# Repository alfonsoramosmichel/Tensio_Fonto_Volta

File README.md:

# Tensio_Fonto_Volta
Fuente de voltaje con salida simétrica +/-12, fija +5 y variable +1.2 - +24

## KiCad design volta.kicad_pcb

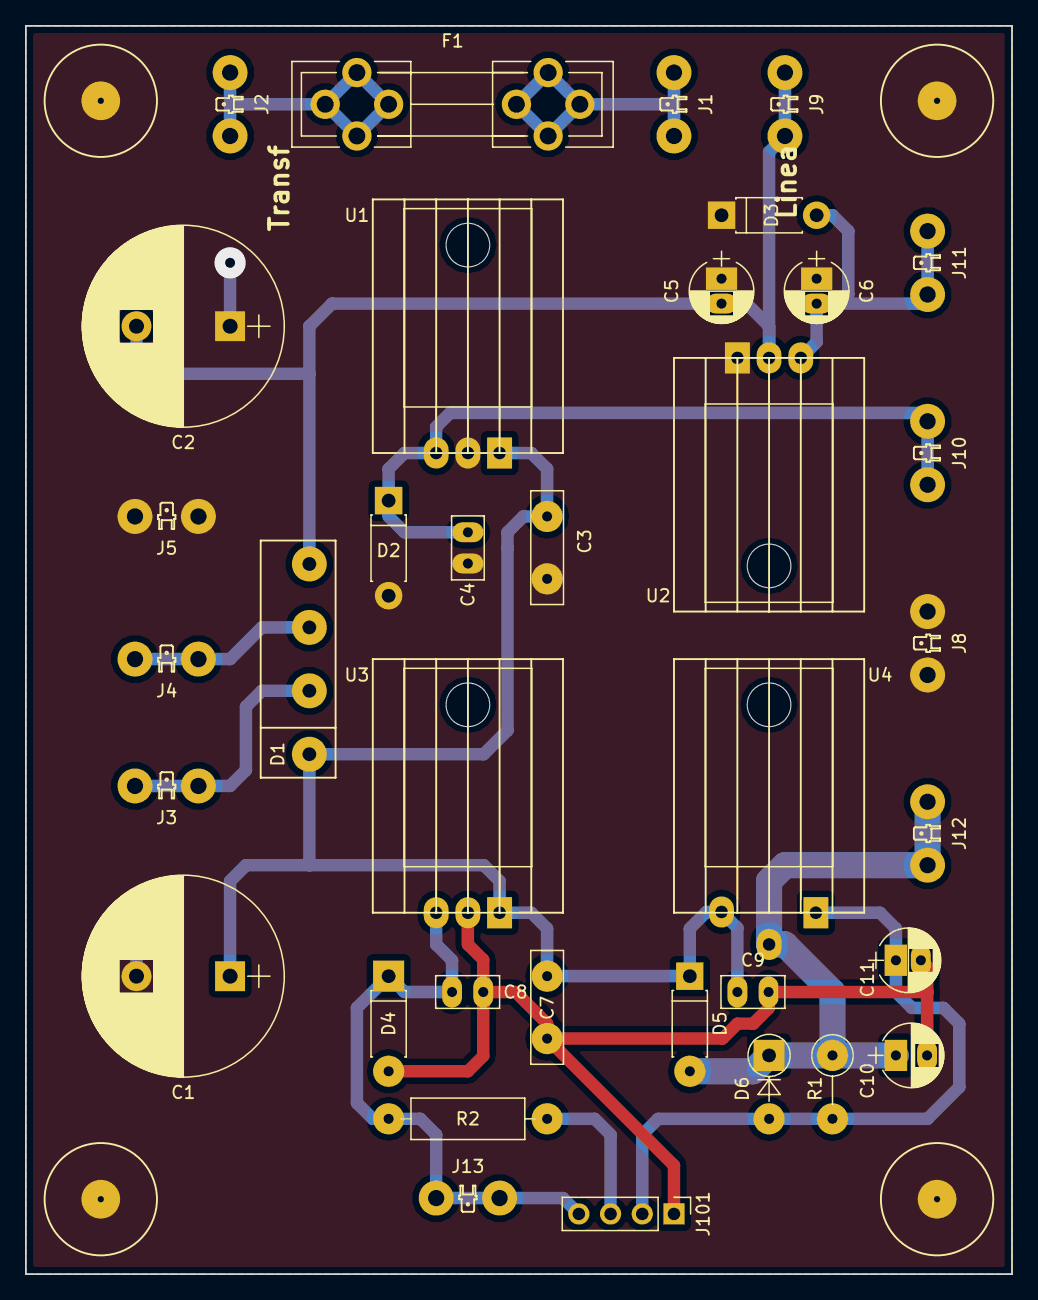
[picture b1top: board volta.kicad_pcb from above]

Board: 2 copper layers, 79.0 x 100.0 mm, 40 parts (0 on the bottom side), 14 nets.

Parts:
C1, C2: 2200uF / 50V; CP_Radial_D16.0mm_P7.50mm
C3, C7: 0.33uF; C_Disc_D9.0mm_W2.5mm_P5.00mm
C4, C8, C9: 0.1uF; C_Disc_D5.0mm_W2.5mm_P2.50mm
C5: 22uF; CP_Radial_D5.0mm_P2.00mm
C6: 1uF; CP_Radial_D5.0mm_P2.00mm
C10: 1uF; CP_Radial_D5.0mm_P2.50mm
C11: 10uF; CP_Radial_D5.0mm_P2.00mm
D1: EXI-KBL406; EXI_KBL406
D2, D3, D4, D5: 1N4007; D_DO-41_SOD81_P7.62mm_Horizontal
D6: 1N4007; D_DO-41_SOD81_P5.08mm_Vertical_AnodeUp
F1: Fusible; Fuseholder5x20_horiz_open_universal_Type-III
J1: AC-vivo; blade_vertical_6.3mm_P5.08mm
J2: Trans-Vivo; blade_vertical_6.3mm_P5.08mm
J3: Trans-V24; blade_vertical_6.3mm_P5.08mm
J4: Trans-N24; blade_vertical_6.3mm_P5.08mm
J5: Deriv; blade_vertical_6.3mm_P5.08mm
J8: GND; blade_vertical_6.3mm_P5.08mm
J9: V-; blade_vertical_6.3mm_P5.08mm
J10: +12; blade_vertical_6.3mm_P5.08mm
J11: -12; blade_vertical_6.3mm_P5.08mm
J12: +Vv; blade_vertical_6.3mm_P5.08mm
J13: +5V; blade_vertical_6.3mm_P5.08mm
J101: Perifericos; Pin_Header_Straight_1x04_Pitch2.54mm
MK1, MK2, MK3, MK4: Mounting_Hole; Tuerca_9mm
R1: 120; R_Axial_DIN0309_L9.0mm_D3.2mm_P5.08mm_Vertical
R2: 470; R_Axial_DIN0309_L9.0mm_D3.2mm_P12.70mm_Horizontal
U1: L7812; TO-220-3_Horizontal_Heatsink_10x15x21mm
U2: L7912; TO-220-3_Horizontal_Heatsink_10x15x21mm
U3: L7805; TO-220-3_Horizontal_Heatsink_10x15x21mm
U4: LM338T; TO-220-3_Horizontal_Heatsink_10x15x21mm

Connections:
+VDC: C1.1, C3.1, C7.1, C9.1, D1.1, D5.1, U1.1, U3.1, U4.3
-VDC: C2.2, C5.2, D1.4, J9.1, U2.2
/+5V: C8.1, D4.1, J13.1, J101.4, R2.1, U3.3
/+12: C4.1, D2.1, J10.1, U1.3
/+Vv: C10.1, D5.2, D6.1, J12.1, R1.1, U4.2
/-12: C6.2, D3.2, J11.1, U2.3
/LED: J101.3, R2.2
/adj: C11.1, D6.2, J101.2, R1.2, U4.1
/n24: D1.3, J4.1
/sw: F1.2, J1.1
/trans: F1.1, J2.1
/v24: D1.2, J3.1
GND: C1.2, C2.1, C3.2, C4.2, C5.1, C6.1, D2.2, D3.1, J5.1, J8.1, U1.2, U2.1
GNDREF: C7.2, C8.2, C9.2, C10.2, C11.2, D4.2, J101.1, U3.2

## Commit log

2018-04-11 Create LICENSE
2018-04-11 Cambios para hacer commit: nuevo archivo: doc/KBL406.pdf nuevo archivo: volta-cache.lib nuevo archivo: volta.kicad_pcb nuevo archivo: volta.pro nuevo archivo: volta.sch
2018-04-14 Trabajo
    Cambios para hacer commit:
    modificado: volta-cache.lib
    modificado: volta.kicad_pcb
    modificado: volta.pro
    modificado: volta.sch
2018-04-16 Cambios menores
    Cambios para hacer commit:
    agregado el modelo 3D del pin hecho en Wings3D al pcb
2018-04-19 Actualización
2018-04-21 Añadido el primer BOM
    Cambios para hacer commit:
    nuevo archivo: bom.ini
    nuevo archivo: volta_bom_.html
2018-04-28 Actualización mayor
    cambio de pin blade 3.6
    cambio de capacitores 3.3uF
    cambio de pines para potenciometros
    cambio de huella para fusible
2018-05-02 nuevo cajetin de udeg
2018-06-21 Borrados archivos no utiles para hacer cambios nuevos
2018-06-22 avanzada en la PCB con plano de tierra
